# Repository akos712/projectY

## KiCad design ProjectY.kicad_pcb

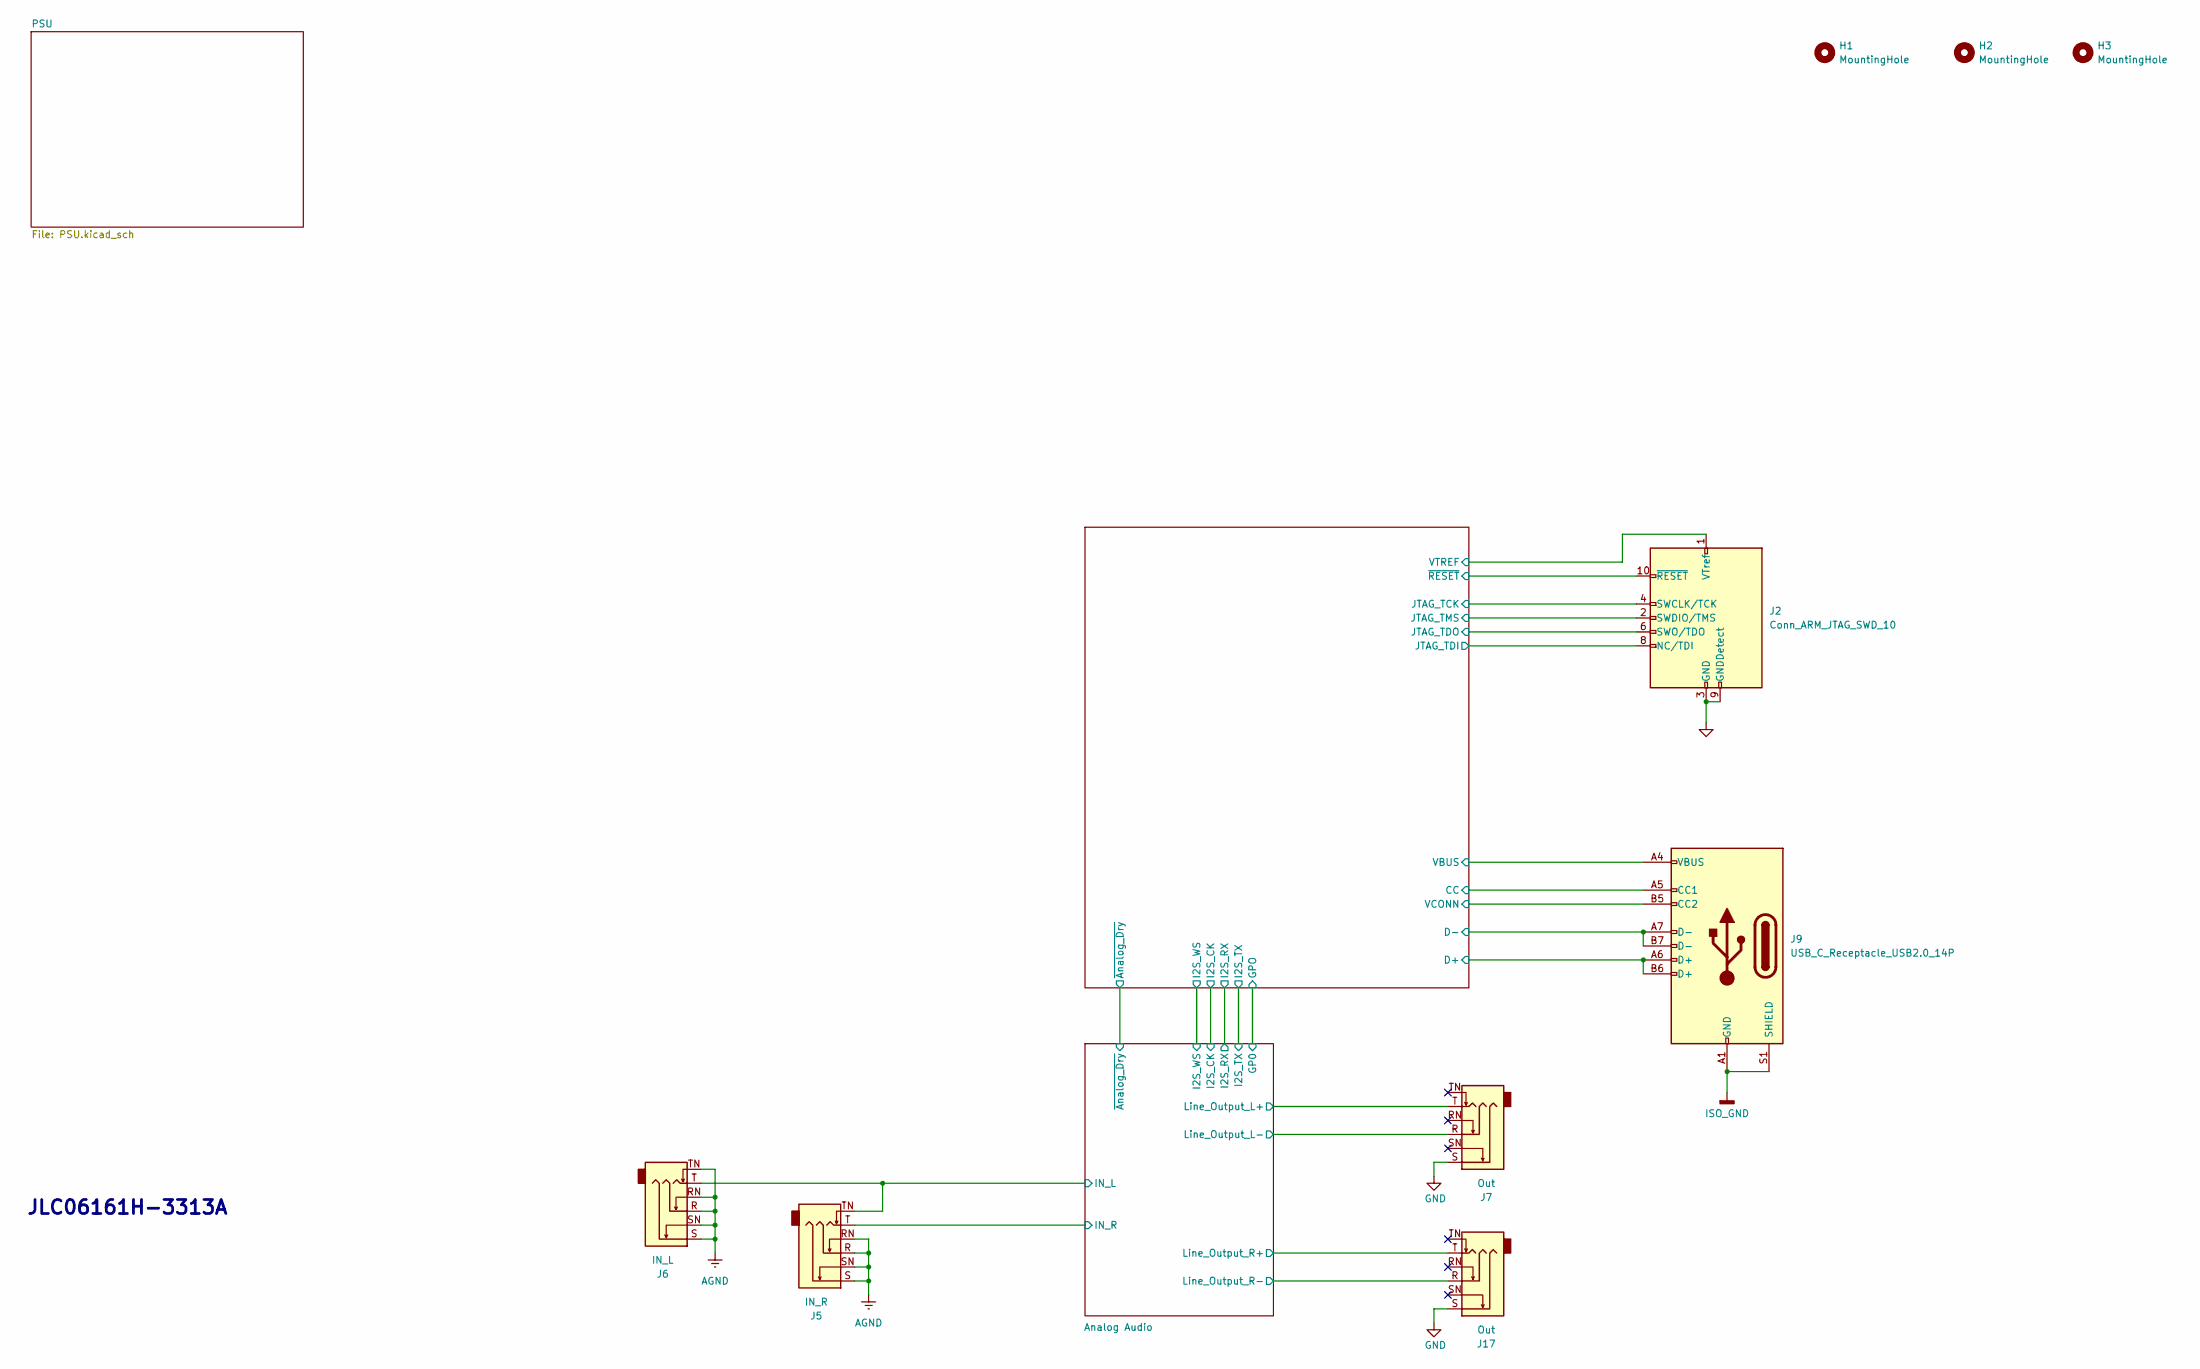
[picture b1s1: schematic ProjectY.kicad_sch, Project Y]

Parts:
H1, H2, H3: MountingHole; MountingHole_2.7mm_M2.5
J2: Conn_ARM_JTAG_SWD_10; PinHeader_2x05_P1.27mm_Vertical_SMD
J5: IN_R; Jack_6.35mm_Neutrik_NRJ6HF_Horizontal
J6: IN_L; Jack_6.35mm_Neutrik_NRJ6HF_Horizontal
J7, J17: Out; Jack_6.35mm_Neutrik_NRJ6HF_Horizontal
J9: USB_C_Receptacle_USB2.0_14P; USB_C_Receptacle_GCT_USB4110

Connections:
+3.3V: J2.1 (VTref); also elsewhere on the board
/Analog Audio/IN_L: J5.TN, J6.T; also elsewhere on the board
/Analog Audio/IN_R: J5.T; also elsewhere on the board
/Analog Audio/Line_Output_L+: J7.T; also elsewhere on the board
/Analog Audio/Line_Output_L-: J7.R; also elsewhere on the board
/Analog Audio/Line_Output_R+: J17.T; also elsewhere on the board
/Analog Audio/Line_Output_R-: J17.R; also elsewhere on the board
/DSP/CC: J9.A5 (CC1); also elsewhere on the board
/DSP/D+: J9.A6 (D+), J9.B6 (D+); also elsewhere on the board
/DSP/D-: J9.A7 (D-), J9.B7 (D-); also elsewhere on the board
/DSP/JTAG_TCK: J2.4 (SWCLK/TCK); also elsewhere on the board
/DSP/JTAG_TDI: J2.8 (NC/TDI); also elsewhere on the board
/DSP/JTAG_TDO: J2.6 (SWO/TDO); also elsewhere on the board
/DSP/JTAG_TMS: J2.2 (SWDIO/TMS); also elsewhere on the board
/DSP/VBUS: J9.A4 (VBUS), J9.A9 (VBUS), J9.B4 (VBUS), J9.B9 (VBUS); also elsewhere on the board
/DSP/VCONN: J9.B5 (CC2); also elsewhere on the board
/DSP/~RESET: J2.10 (~RESET); also elsewhere on the board
AGND: J5.R, J5.RN, J5.S, J5.SN, J6.R, J6.RN, J6.S, J6.SN, J6.TN; also elsewhere on the board
GND: J2.3 (GND), J2.5 (GND), J2.9 (GNDDetect), J7.S, J17.S; also elsewhere on the board
ISO_GND: J9.A1 (GND), J9.A12 (GND), J9.B1 (GND), J9.B12 (GND), J9.S1 (SHIELD); also elsewhere on the board

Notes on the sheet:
JLC06161H-3313A

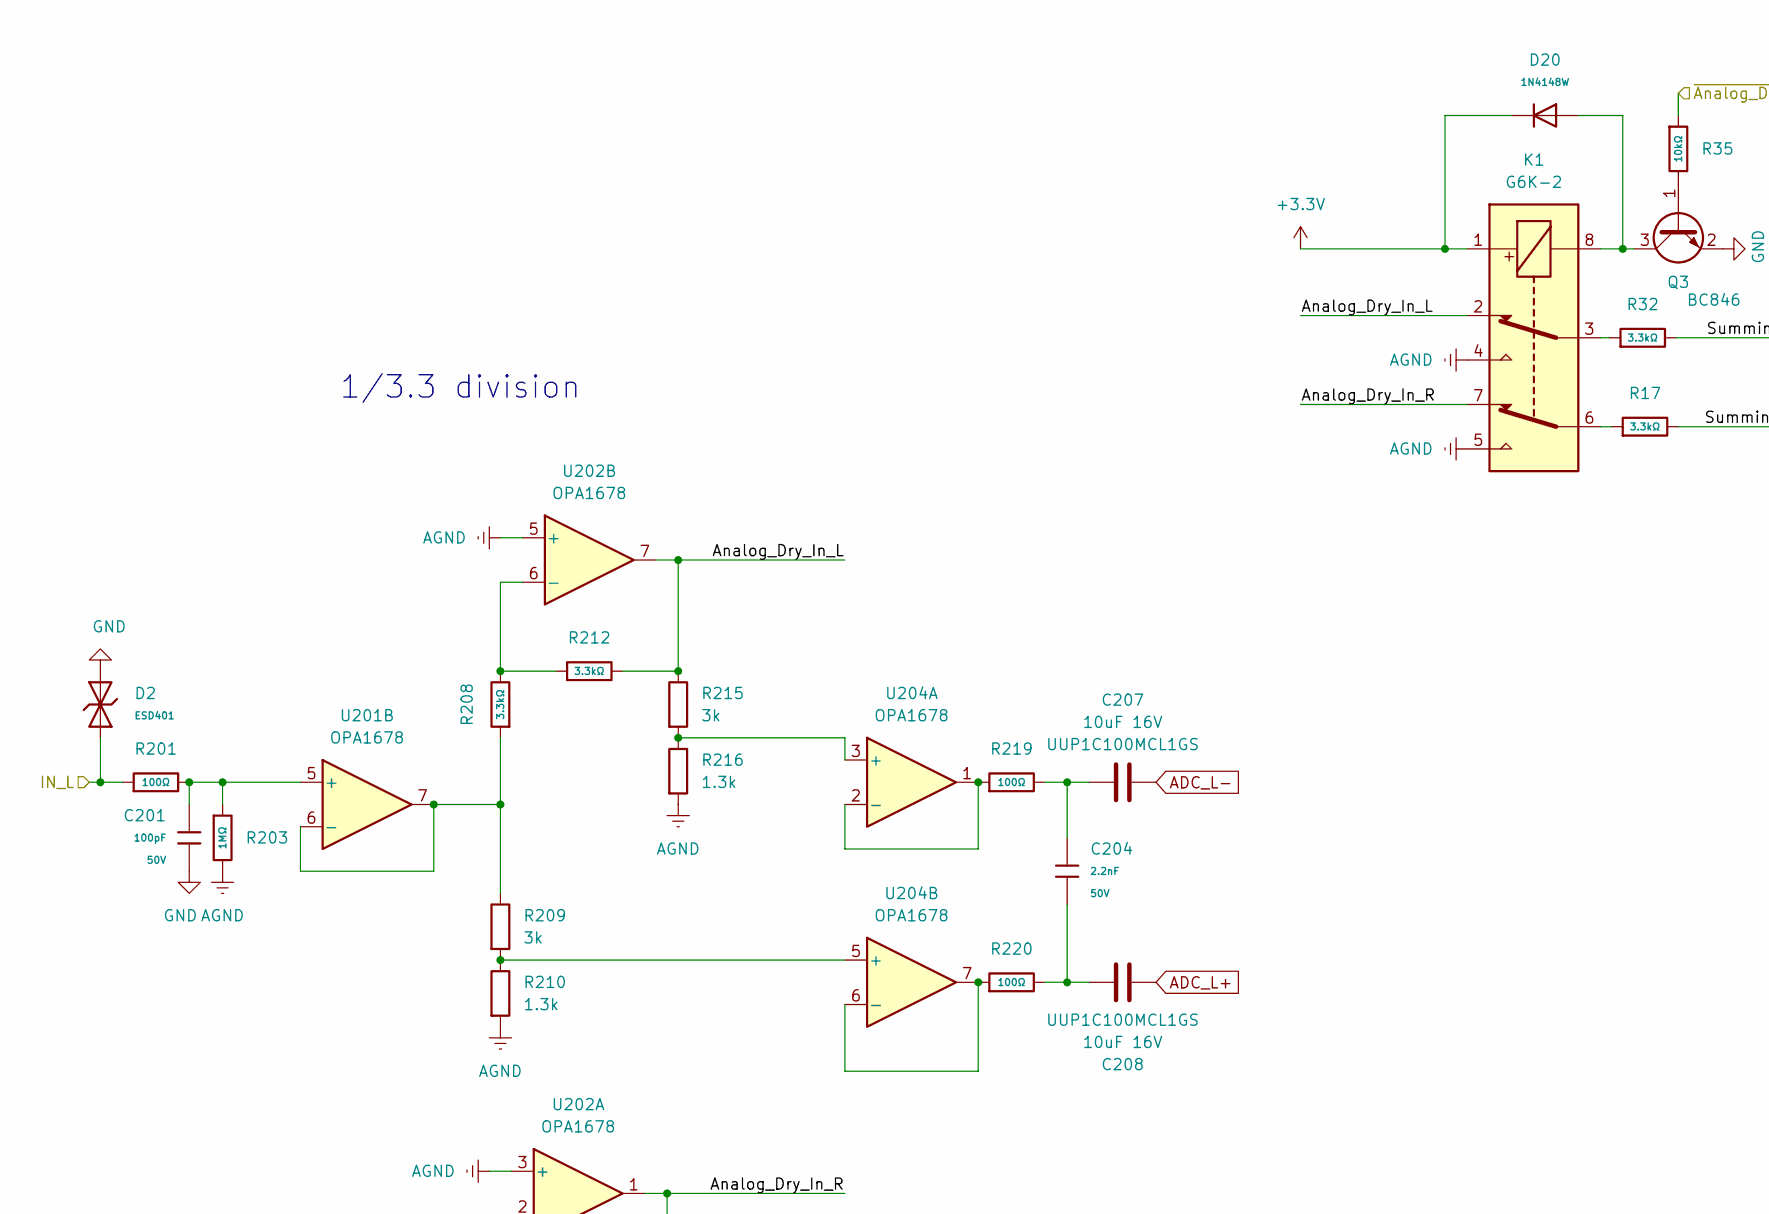
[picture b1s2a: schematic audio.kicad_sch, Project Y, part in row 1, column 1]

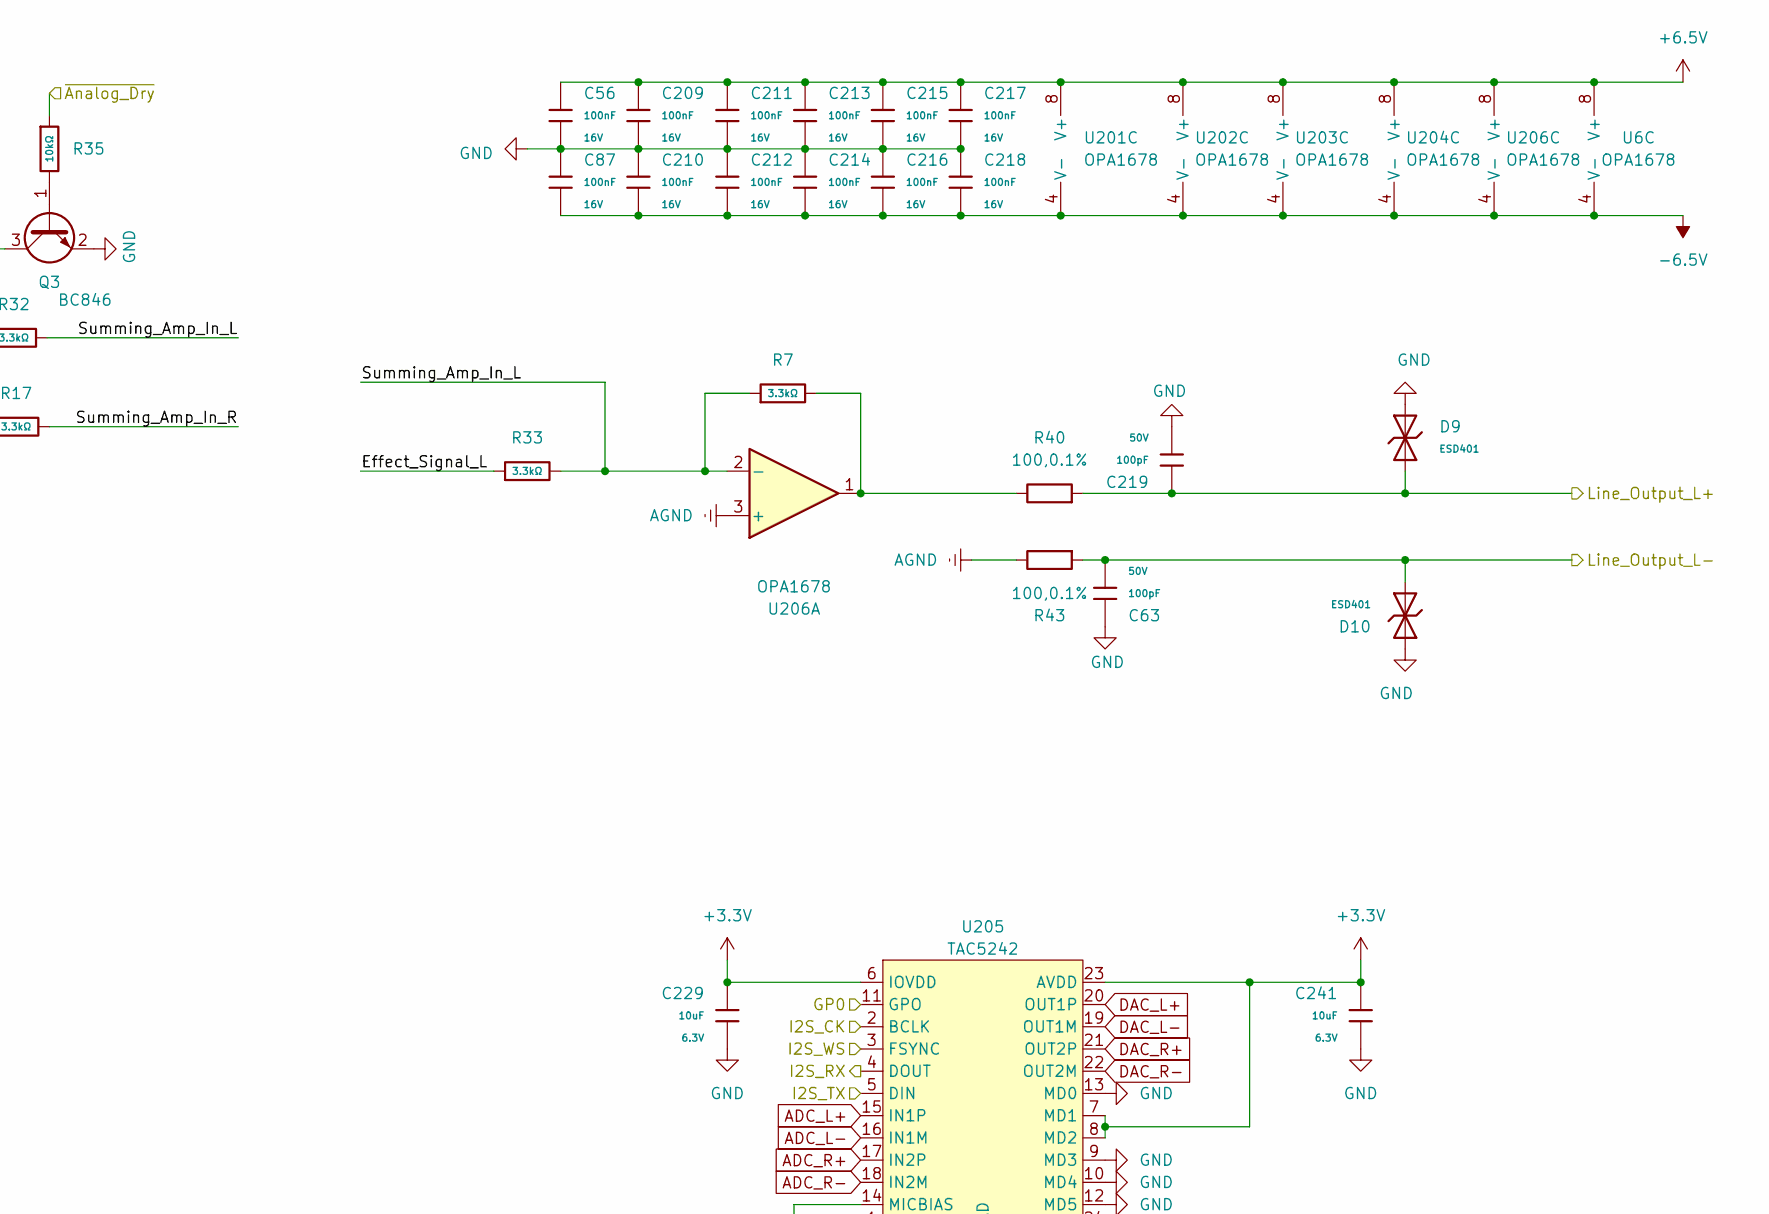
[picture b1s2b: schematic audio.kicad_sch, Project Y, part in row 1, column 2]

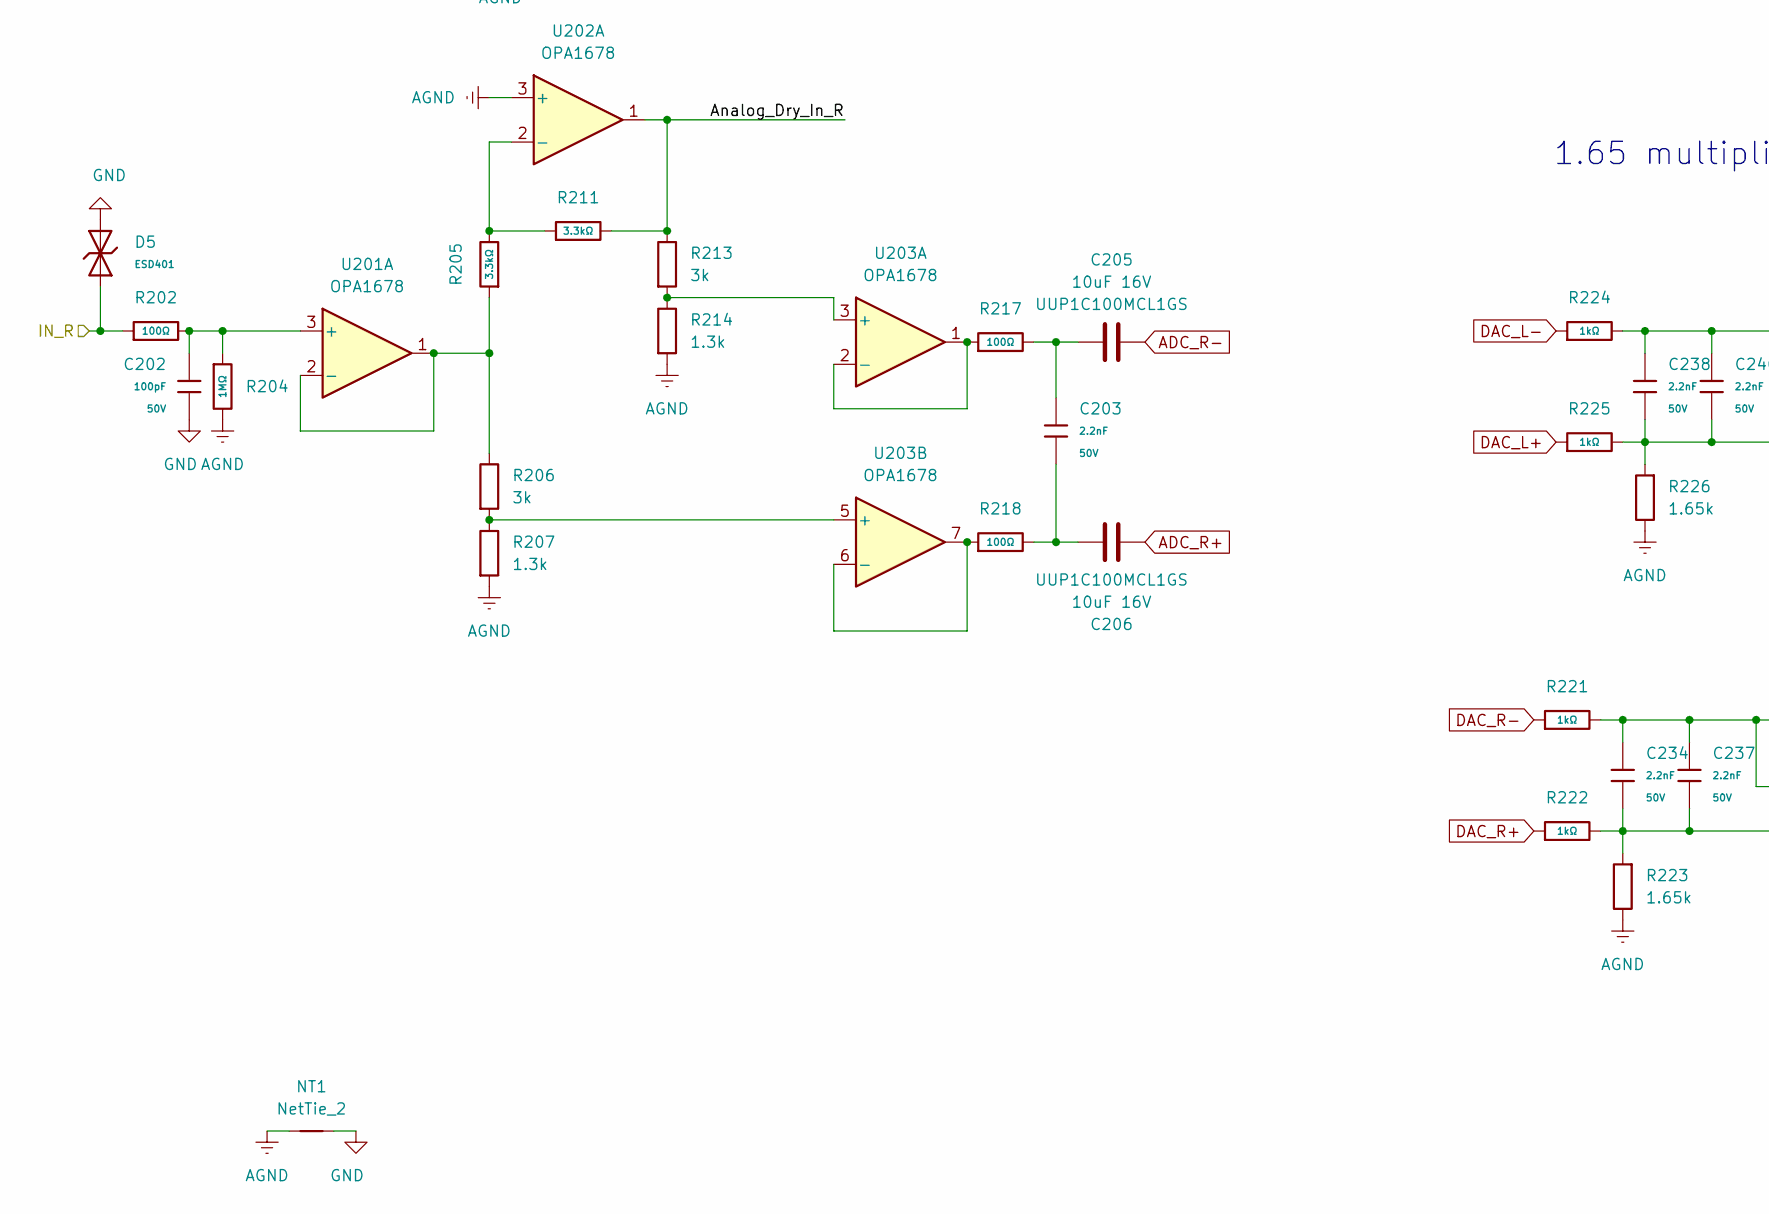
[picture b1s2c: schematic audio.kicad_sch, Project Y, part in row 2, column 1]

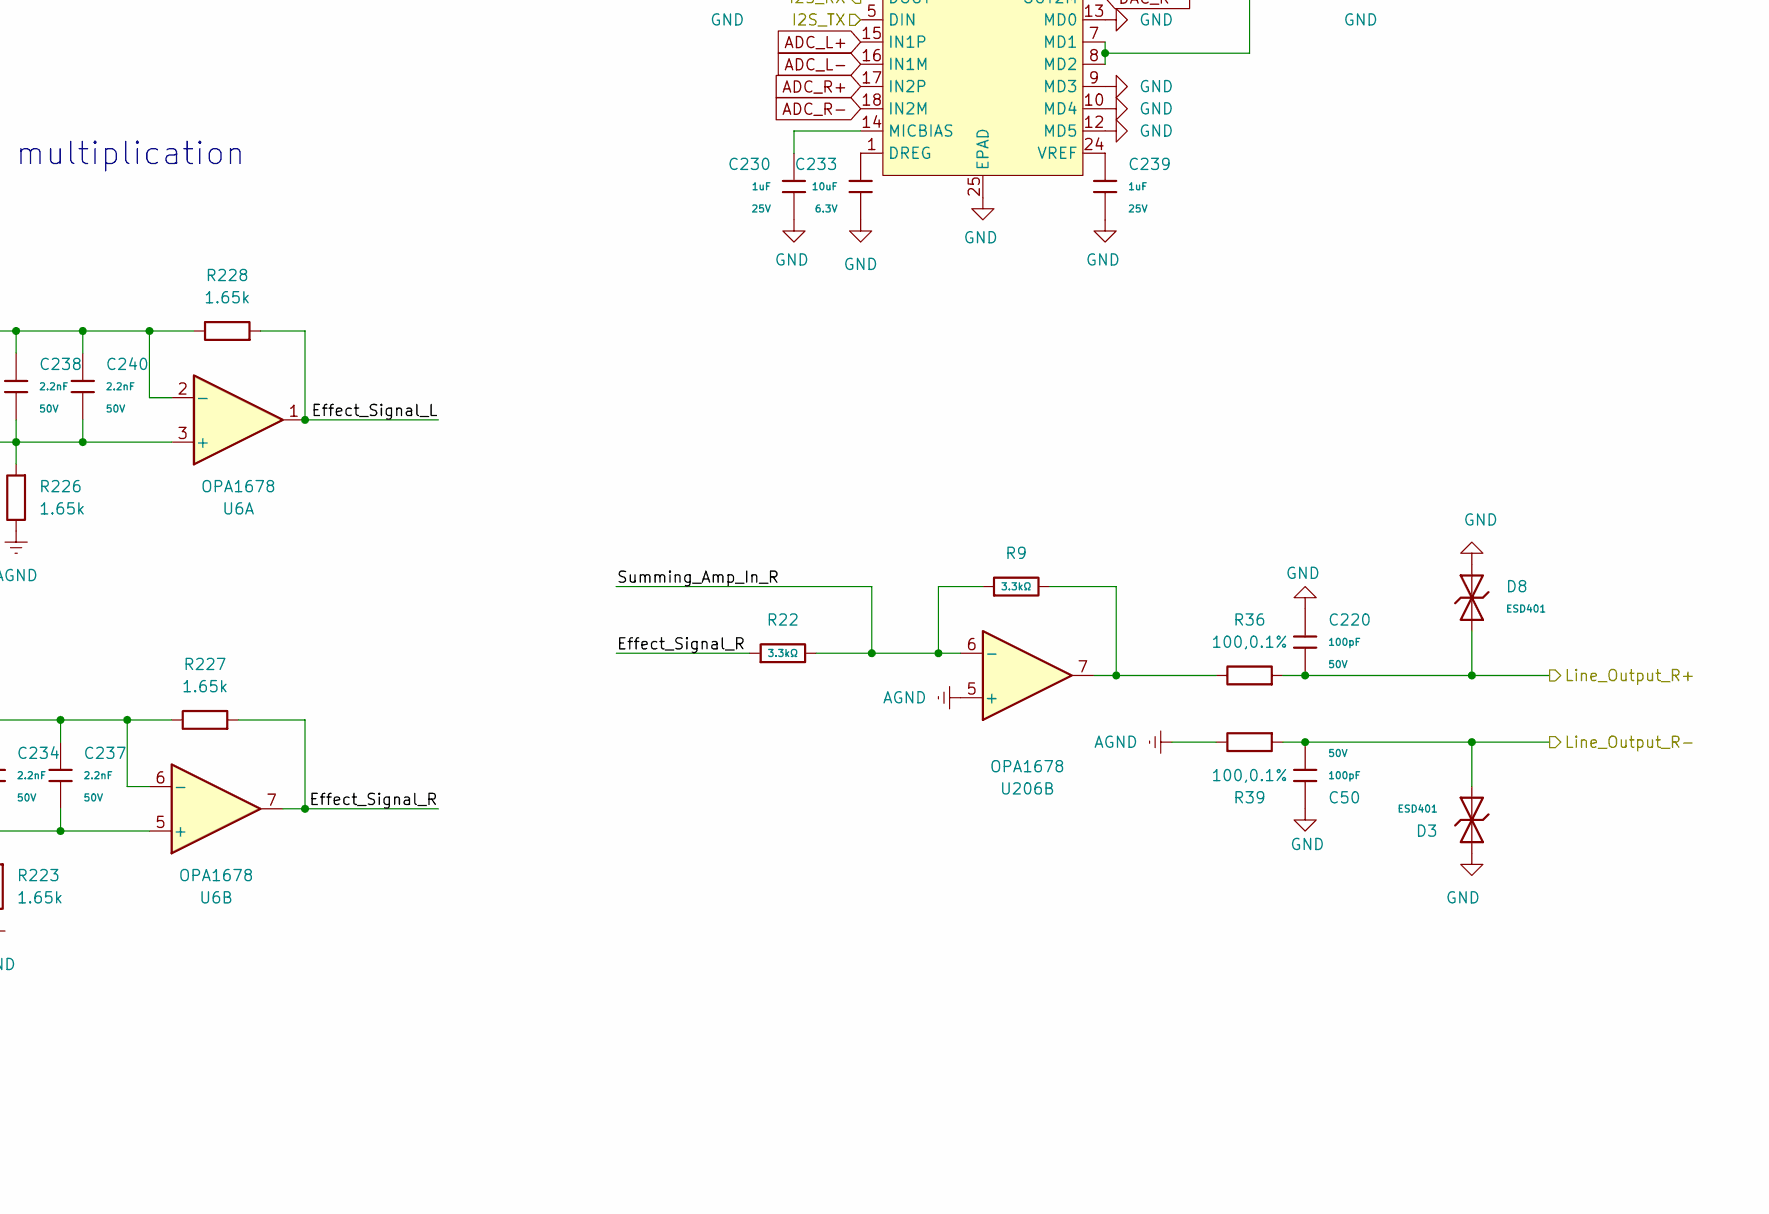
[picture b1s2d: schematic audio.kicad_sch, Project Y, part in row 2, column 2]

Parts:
C50, C63, C201, C202, C219, C220: 100pF; C_0402; Voltage Rated 50V; Tolerance ±5%; Part 0402CG101J500NT; LCSC C1546
C56, C87, C209, C210, C211, C212, C213, C214, C215, C216, C217, C218: 100nF; C_0402; Voltage Rated 16V; Tolerance ±10%; Part CL05B104KO5NNNC; LCSC C1525
C203, C204, C234, C237, C238, C240: 2.2nF; C_0805; Voltage Rated 50V; Tolerance ±5%; Part CL21C222JBFNNNE; LCSC C28260
C205, C206, C207, C208: 10uF 16V; C_Elec_5x5.8; LCSC C1984751
C229, C233, C241: 10uF; C_0402; Voltage Rated 6.3V; Tolerance ±20%; Part CL05A106MQ5NUNC; LCSC C15525
C230, C239: 1uF; C_0402; Voltage Rated 25V; Tolerance ±10%; Part CL05A105KA5NQNC; LCSC C52923
D2, D3, D5, D8, D9, D10: ESD401; D_DFN1006-2L; Clamping Voltage@Ipp 10V; Breakdown Voltage (VBR) 5.6V; Part H5VL10B; LCSC C7420372
D20: 1N4148W; D_SOD-123; Forward Voltage (Vf@If) 1V@50mA; Reverse Voltage (Vr) 75V; Part 1N4148W; LCSC C81598
K1: G6K-2; Relay_DPDT_Omron_G6K-2F-Y
NT1: NetTie_2; NetTie-2_SMD_Pad0.5mm
Q3: BC846; SOT-23
R7, R9, R17, R22, R32, R33, R205, R208, R211, R212: 3.3kΩ; R_0402; Overload Voltage (Max) 50V; Tolerance ±1%; Part 0402WGF3301TCE; LCSC C25890
R35: 10kΩ; R_0402; Overload Voltage (Max) 50V; Tolerance ±1%; Part 0402WGF1002TCE; LCSC C25744
R36, R39, R40, R43: 100,0.1%; R_0805_2012Metric
R201, R202, R217, R218, R219, R220: 100Ω; R_0402; Overload Voltage (Max) 50V; Tolerance ±1%; Part 0402WGF1000TCE; LCSC C25076
R203, R204: 1MΩ; R_0402; Overload Voltage (Max) 50V; Tolerance ±1%; Part 0402WGF1004TCE; LCSC C26083
R206, R209, R213, R215: 3k; R_0402
R207, R210, R214, R216: 1.3k; R_0402
R221, R222, R224, R225: 1kΩ; R_0402; Overload Voltage (Max) 50V; Tolerance ±1%; Part 0402WGF1001TCE; LCSC C11702
R223, R227: 1.65k; R_0402_1005Metric
R226, R228: 1.65k; R_0402
U6, U201, U202, U203, U204: OPA1678; VSSOP-8_3x3mm_P0.65mm
U205: TAC5242
U206: OPA1678; SOIC-8_3.9x4.9mm_P1.27mm

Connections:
+3.3V: C229.1, C241.1, D20.1, K1.1, U205.6 (IOVDD), U205.7 (MD1), U205.8 (MD2), U205.23 (AVDD); also elsewhere on the board
+6.5V: C56.1, C209.1, C211.1, C213.1, C215.1, C217.1, U6.8 (V+), U201.8 (V+), U202.8 (V+), U203.8 (V+), U204.8 (V+), U206.8 (V+); also elsewhere on the board
-6.5V: C87.2, C210.2, C212.2, C214.2, C216.2, C218.2, U6.4 (V-), U201.4 (V-), U202.4 (V-), U203.4 (V-), U204.4 (V-), U206.4 (V-); also elsewhere on the board
/Analog Audio/Analog_Dry_In_L: K1.2, R212.2, R215.1, U202.7
/Analog Audio/Analog_Dry_In_R: K1.7, R211.2, R213.1, U202.1
/Analog Audio/Effect_Signal_L: R33.1, R228.2, U6.1
/Analog Audio/Effect_Signal_R: R22.1, R227.2, U6.7
/Analog Audio/GP0: U205.11 (GPO); also elsewhere on the board
/Analog Audio/I2S_CK: U205.2 (BCLK); also elsewhere on the board
/Analog Audio/I2S_RX: U205.4 (DOUT); also elsewhere on the board
/Analog Audio/I2S_TX: U205.5 (DIN); also elsewhere on the board
/Analog Audio/I2S_WS: U205.3 (FSYNC); also elsewhere on the board
/Analog Audio/IN_L: D2.1, R201.1; also elsewhere on the board
/Analog Audio/IN_R: D5.1, R202.1; also elsewhere on the board
/Analog Audio/Line_Output_L+: C219.1, D9.1, R40.2; also elsewhere on the board
/Analog Audio/Line_Output_L-: C63.2, D10.1, R43.2; also elsewhere on the board
/Analog Audio/Line_Output_R+: C220.2, D8.1, R36.2; also elsewhere on the board
/Analog Audio/Line_Output_R-: C50.2, D3.1, R39.2; also elsewhere on the board
/Analog Audio/Summing_Amp_In_L: R7.1, R32.2, R33.2, U206.2 (-)
/Analog Audio/Summing_Amp_In_R: R9.1, R17.2, R22.2, U206.6 (-)
/Analog Audio/~Analog_Dry: R35.1; also elsewhere on the board
ADC_L+: C208.1, U205.15 (IN1P)
ADC_L-: C207.1, U205.16 (IN1M)
ADC_R+: C206.1, U205.17 (IN2P)
ADC_R-: C205.1, U205.18 (IN2M)
AGND: K1.4, K1.5, NT1.1, R39.1, R43.1, R203.2, R204.2, R207.2, R210.2, R214.2, R216.2, R223.1, R226.1, U202.3 (+), U202.5 (+), U206.3 (+), U206.5 (+); also elsewhere on the board
DAC_L+: R225.1, U205.20 (OUT1P)
DAC_L-: R224.1, U205.19 (OUT1M)
DAC_R+: R222.1, U205.21 (OUT2P)
DAC_R-: R221.1, U205.22 (OUT2M)
GND: C50.1, C56.2, C63.1, C87.1, C201.2, C202.2, C209.2, C210.1, C211.2, C212.1, C213.2, C214.1, C215.2, C216.1, C217.2, C218.1, C219.2, C220.1, C229.2, C230.2, C233.2, C239.2, C241.2, D2.2, D3.2, D5.2, D8.2, D9.2, D10.2, NT1.2, Q3.2 (E), U205.9 (MD3), U205.10 (MD4), U205.12 (MD5), U205.13 (MD0), U205.25 (EPAD), U205.A1 (VSS), U205.A2 (VSS), U205.A3 (VSS), U205.A4 (VSS); also elsewhere on the board
unnamed: C203.1, C206.2, R218.2
unnamed: C203.2, C205.2, R217.2
unnamed: C204.1, C208.2, R220.2
unnamed: C204.2, C207.2, R219.2
unnamed: K1.3, R32.1
unnamed: K1.6, R17.1
unnamed: Q3.1 (B), R35.2
unnamed: D20.2, K1.8, Q3.3 (C)
unnamed: R9.2, R36.1, U206.7
unnamed: R7.2, R40.1, U206.1
unnamed: C238.1, C240.1, R225.2, R226.2, U6.3 (+)
unnamed: C238.2, C240.2, R224.2, R228.1, U6.2 (-)
unnamed: C234.1, C237.1, R222.2, R223.2, U6.5 (+)
unnamed: C234.2, C237.2, R221.2, R227.1, U6.6 (-)
unnamed: C202.1, R202.2, R204.1, U201.3 (+)
unnamed: R205.1, R206.1, U201.1, U201.2 (-)
unnamed: C201.1, R201.2, R203.1, U201.5 (+)
unnamed: R208.1, R209.1, U201.6 (-), U201.7
unnamed: R205.2, R211.1, U202.2 (-)
unnamed: R208.2, R212.1, U202.6 (-)
unnamed: R213.2, R214.1, U203.3 (+)
unnamed: R217.1, U203.1, U203.2 (-)
unnamed: R206.2, R207.1, U203.5 (+)
unnamed: R218.1, U203.6 (-), U203.7
unnamed: R215.2, R216.1, U204.3 (+)
unnamed: R219.1, U204.1, U204.2 (-)
unnamed: R209.2, R210.1, U204.5 (+)
unnamed: R220.1, U204.6 (-), U204.7
unnamed: C233.1, U205.1 (DREG)
unnamed: C230.1, U205.14 (MICBIAS)
unnamed: C239.1, U205.24 (VREF)

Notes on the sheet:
1.65 multiplication
1/3.3 division
